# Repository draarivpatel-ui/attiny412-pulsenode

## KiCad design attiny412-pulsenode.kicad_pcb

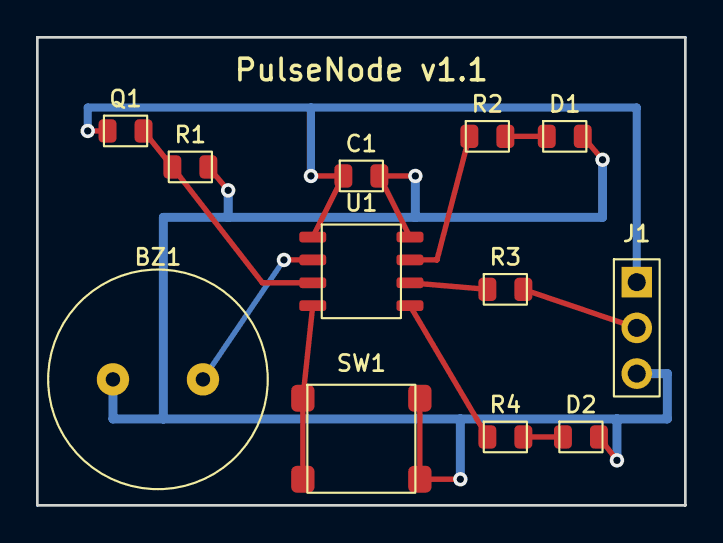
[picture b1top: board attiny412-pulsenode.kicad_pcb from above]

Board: 2 copper layers, 36.0 x 26.0 mm, 12 parts (0 on the bottom side), 11 nets.

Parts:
BZ1: Piezo Transducer 12mm; MagneticBuzzer_12x12mm
C1: 100nF 50V X7R; C_0805_2012Metric
D1: Amber PWM LED; LED_0805_2012Metric
D2: Emerald Status LED; LED_0805_2012Metric
J1: UPDI Power Header; PinHeader_1x03_P2.54mm_Vertical
Q1: ALS-PT19 Phototransistor; LED_0805_2012Metric
R1: 10k Ohm 1%; R_0805_2012Metric
R2, R4: 330 Ohm 1%; R_0805_2012Metric
R3: 4.7k Ohm UPDI; R_0805_2012Metric
SW1: PTS645 Tactile Switch; SW_SPST_PTS645
U1: ATtiny412-SSNR; SOIC-8_3.9x4.9mm_P1.27mm

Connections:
+5V: C1.1, J1.1, Q1.1, U1.1
GND: BZ1.2, C1.2, D1.2, D2.2, J1.3, R1.2, SW1.3, SW1.4, U1.8
PA0_UPDI: R3.1, U1.6
PA1_BTN: SW1.1, SW1.2, U1.4
PA2_STATUS: R4.1, U1.5
PA3_PWM: R2.1, U1.7
PA6_PIEZO: BZ1.1, U1.2
PA7_LDR: Q1.2, R1.1, U1.3
PWM_LED: D1.1, R2.2
STATUS_LED: D2.1, R4.2
UPDI_HDR: J1.2, R3.2

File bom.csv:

Reference,Value,Footprint,Quantity,MPN,Supplier,Unit_Cost_USD
U1,ATtiny412-SSNR,Package_SO:SOIC-8_3.9x4.9mm_P1.27mm,1,ATTINY412-SSNR,DigiKey,0.58
C1,100nF 50V X7R,Capacitor_SMD:C_0805_2012Metric,1,CL21B104KBCNNNC,LCSC,0.02
R1,10k Ohm 1%,Resistor_SMD:R_0805_2012Metric,1,RC0805FR-0710KL,LCSC,0.01
R2,330 Ohm 1%,Resistor_SMD:R_0805_2012Metric,1,RC0805FR-07330RL,LCSC,0.01
R3,4.7k Ohm UPDI,Resistor_SMD:R_0805_2012Metric,1,RC0805FR-074K7L,LCSC,0.01
R4,330 Ohm 1%,Resistor_SMD:R_0805_2012Metric,1,RC0805FR-07330RL,LCSC,0.01
D1,Amber PWM LED,LED_SMD:LED_0805_2012Metric,1,KT-0805Y,LCSC,0.03
D2,Emerald Status LED,LED_SMD:LED_0805_2012Metric,1,KT-0805G,LCSC,0.03
Q1,ALS-PT19 Phototransistor,LED_SMD:LED_0805_2012Metric,1,ALS-PT19-315C/L177/TR8,DigiKey,0.24
SW1,PTS645 Tactile Switch,Button_Switch_SMD:SW_SPST_PTS645,1,PTS645SM43SMTR92LFS,LCSC,0.12
BZ1,Piezo Transducer 12mm,Buzzer_Beeper:MagneticBuzzer_12x12mm,1,PS1240P02BT,DigiKey,0.65
J1,1x03 UPDI Pin Header,Connector_PinHeader_2.54mm:PinHeader_1x03_P2.54mm_Vertical,1,PH1-03-UA,LCSC,0.05
